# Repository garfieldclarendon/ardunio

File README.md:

# Layout Control System (LCS)

A project that uses ESP8266 WiFi modules that communicate with a Raspberry Pi server to control accessories on the Garfield-Clarendon Model Railroad Club.

### Prerequisites

The code running on the ESP8266 is developed using the Arduino IDE

The LCSServer application running on the Raspberry Pi makes use of the Qt framework.  The ESP8266 uses http calls to communicate with the LCSServer application  and UDP unicast messages to communicate with other ESP8266 controllers on the layout.  A separate RESTful API provides access to commands to activate routes, set turnouts and update data in the configuration database.

[Layout Control System Overview](https://github.com/garfieldclarendon/garfieldclarendon.github.io/blob/master/html/Documents/LCSOverview.pdf)

[Source Code Documentation](https://garfieldclarendon.github.io/html/index.html)

[API Documentation](https://garfieldclarendon.github.io/apidoc/index.html)

## Built With

* [Arduino](https://www.arduino.cc/en/Main/Software) - Arduino Tools
* [Qt](https://www.qt.io/) - Qt Framework
* [Eagle](https://www.autodesk.com/products/eagle/overview) - Eagle Printed Circuit Board (PCB) design software

## Contributing

Please read [CONTRIBUTING.md](https://gist.github.com/PurpleBooth/b24679402957c63ec426) for details on our code of conduct, and the process for submitting pull requests to us.

## Authors

* **John Reilly** - *Initial work*
* **Ryan Balla** - *Web Development*

## License

This project is licensed under the MIT License - see the [LICENSE](LICENSE) file for details

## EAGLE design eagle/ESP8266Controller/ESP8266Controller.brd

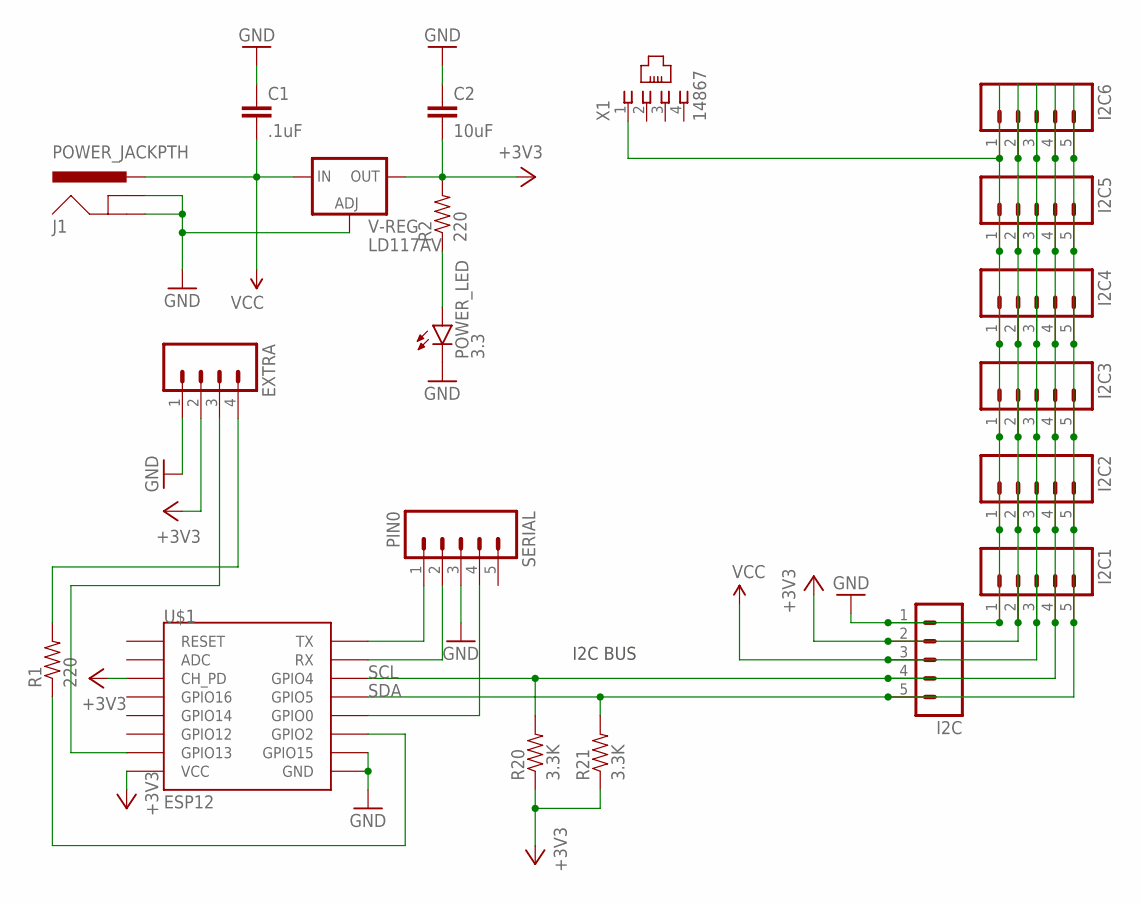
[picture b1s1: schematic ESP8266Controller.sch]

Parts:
C1: .1uF; CAP-PTH-SMALL
C2: 10uF; CAP-PTH-SMALL
EXTRA: M04; 04P
I2C, I2C1, I2C2, I2C3, I2C4, I2C5, I2C6: M05; 05P
J1: POWER_JACKPTH; POWER_JACK_PTH
POWER_LED: 3.3; LED5MM
R1, R2: 220; AXIAL-0.4
R20, R21: 3.3K; AXIAL-0.4
SERIAL: PIN0; 05P
U$1: ESP12
V-REG: LD117AV; TO220L1
X1: 14867

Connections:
+3V3: C2.2, EXTRA.2, I2C.2, I2C1.2, I2C2.2, I2C3.2, I2C4.2, I2C5.2, I2C6.2, R2.P$2 (2), R20.P$1 (1), R21.P$1 (1), U$1.CH_PD, U$1.VCC, V-REG.2 (OUT)
GND: C1.1, C2.1, EXTRA.1, I2C.1, I2C1.1, I2C2.1, I2C3.1, I2C4.1, I2C5.1, I2C6.1, J1.GND, J1.GNDBREAK, POWER_LED.K (C), SERIAL.3, U$1.GND, U$1.GPIO15, V-REG.1 (ADJ), X1.1
unnamed: EXTRA.4, R1.P$2 (2)
unnamed: R1.P$1 (1), U$1.GPIO2
unnamed: EXTRA.3, U$1.GPIO13
unnamed: SERIAL.1, U$1.TX
unnamed: POWER_LED.A, R2.P$1 (1)
unnamed: SERIAL.2, U$1.RX
unnamed: SERIAL.4, U$1.GPIO0
SCL: I2C.4, I2C1.4, I2C2.4, I2C3.4, I2C4.4, I2C5.4, I2C6.4, R20.P$2 (2), U$1.GPIO4
SDA: I2C.5, I2C1.5, I2C2.5, I2C3.5, I2C4.5, I2C5.5, I2C6.5, R21.P$2 (2), U$1.GPIO5
VCC: C1.2, I2C.3, I2C1.3, I2C2.3, I2C3.3, I2C4.3, I2C5.3, I2C6.3, J1.PWR, V-REG.3 (IN)

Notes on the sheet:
I2C BUS

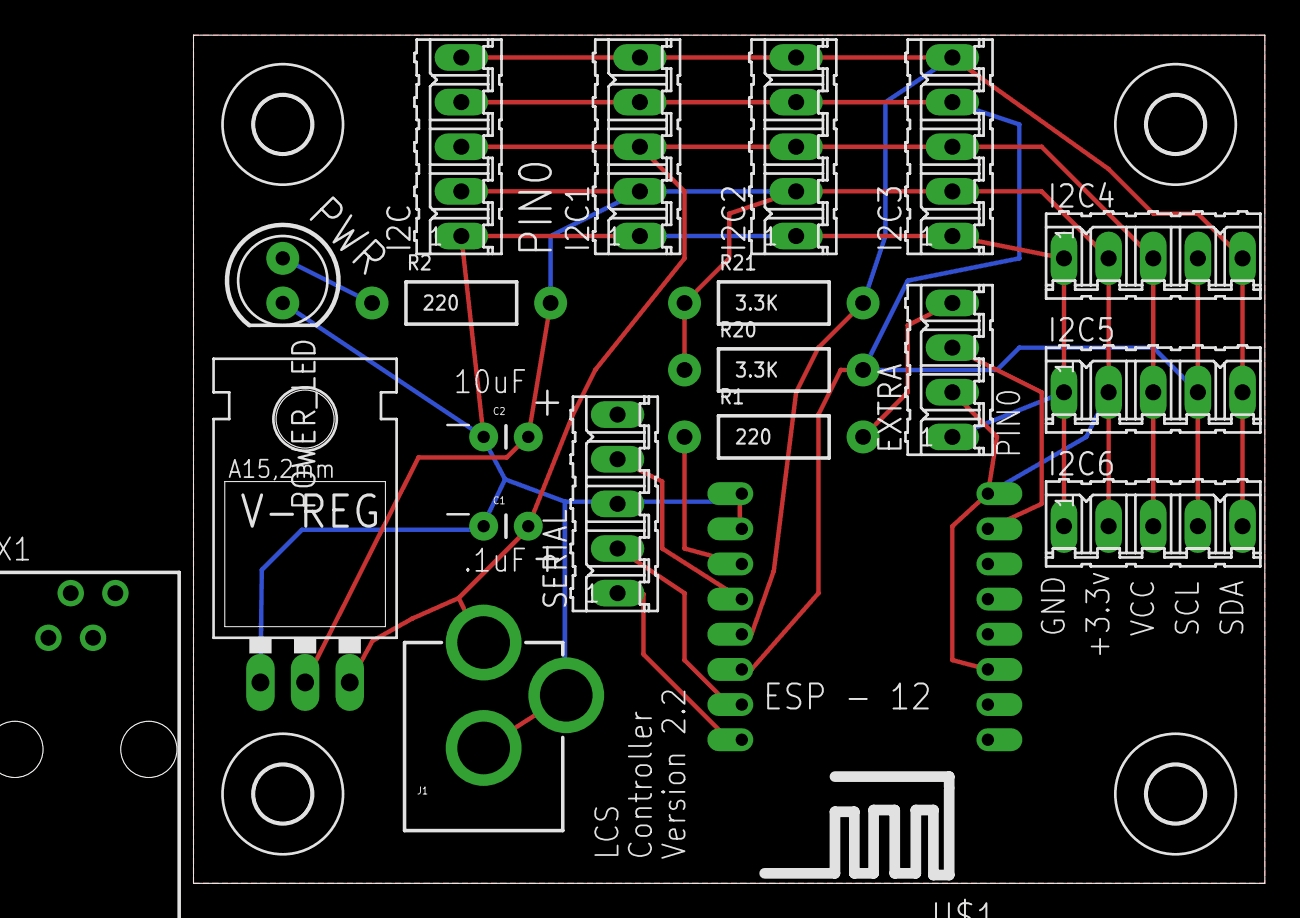
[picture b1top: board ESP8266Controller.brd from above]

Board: 2 copper layers, 61.0 x 48.3 mm, 24 parts (0 on the bottom side), 12 nets.

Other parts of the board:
U$2, U$3, U$4, U$5: 3,2

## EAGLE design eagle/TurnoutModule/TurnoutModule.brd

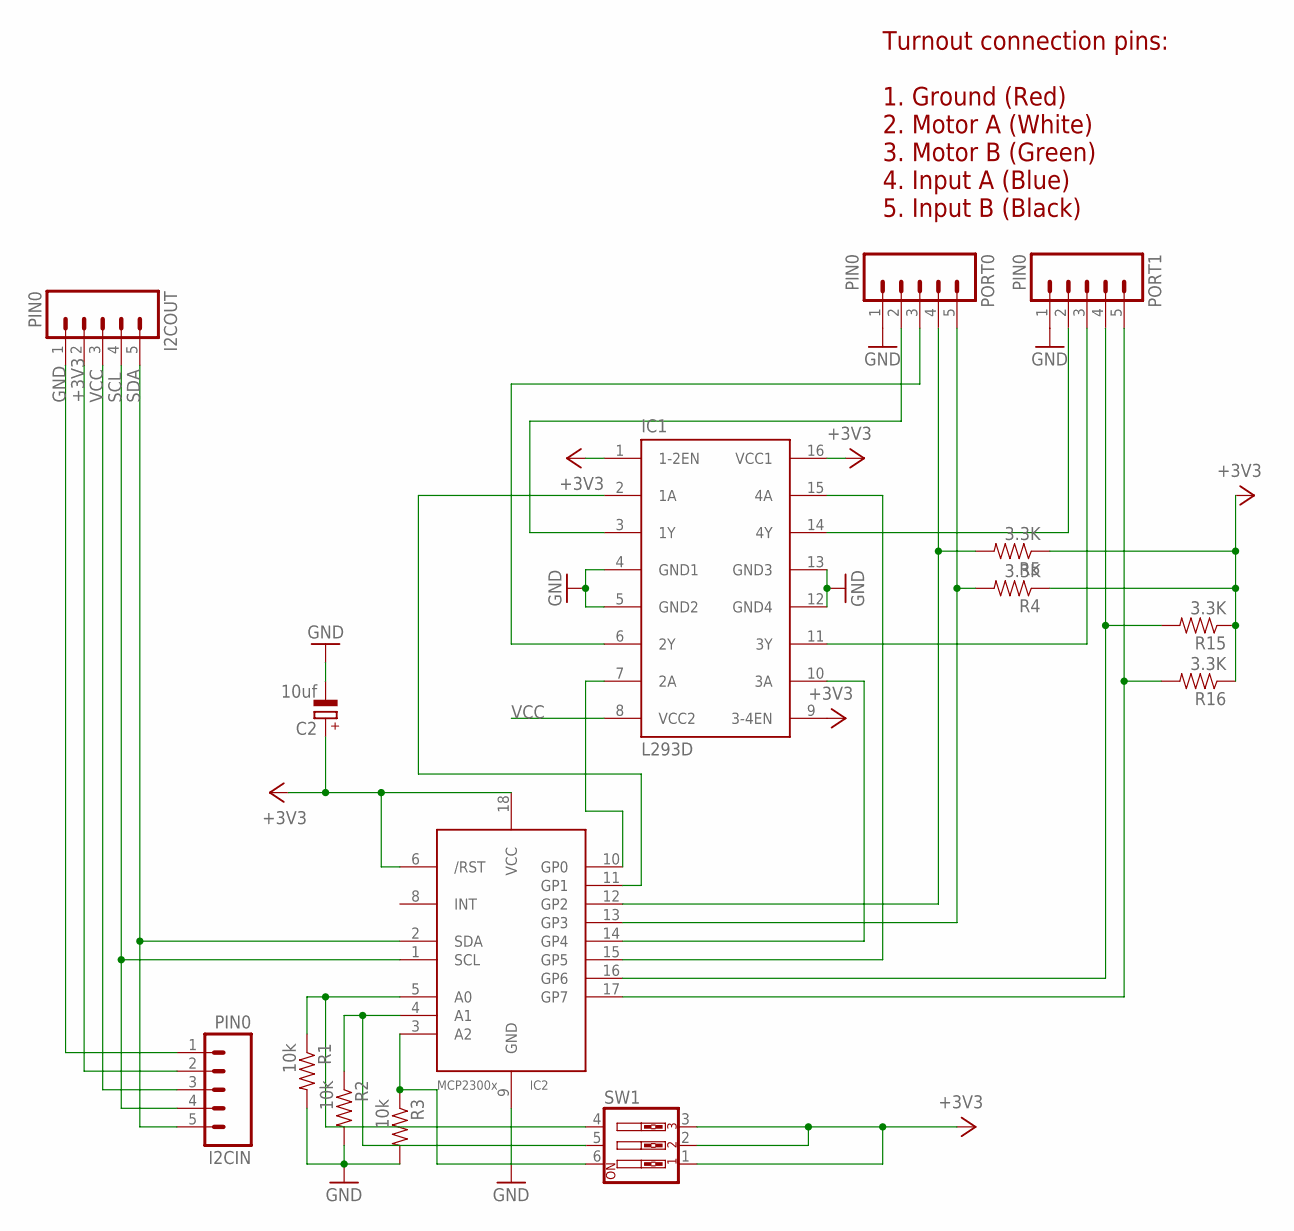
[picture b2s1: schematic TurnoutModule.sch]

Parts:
C2: 10uf; E2,5-6
I2CIN, I2COUT: PIN0; 05P
IC1: L293D; DIL16
IC2: MCP23008/P; DIL18
PORT0, PORT1: PIN0; 05P
R1, R2, R3: 10k; AXIAL-0.4
R4, R5, R15, R16: 3.3K; AXIAL-0.4
SW1: SW_DIP-3; EDG-03

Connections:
+3V3: C2.+, I2CIN.2, I2COUT.2, IC1.1 (1-2EN), IC1.9 (3-4EN), IC1.16 (VCC1), IC2.6 (/RST), IC2.18 (VCC), R4.P$1 (1), R5.P$1 (1), R15.P$1 (1), R16.P$1 (1), SW1.1, SW1.2, SW1.3
GND: C2.-, I2CIN.1, I2COUT.1, IC1.4 (GND1), IC1.5 (GND2), IC1.12 (GND4), IC1.13 (GND3), IC2.9 (GND), PORT0.1, PORT1.1, R1.P$2 (2), R2.P$2 (2), R3.P$2 (2)
unnamed: IC2.5 (A0), R1.P$1 (1), SW1.4
unnamed: IC2.17 (GP7), PORT1.5, R16.P$2 (2)
unnamed: IC1.3 (1Y), PORT0.2
unnamed: IC2.4 (A1), R2.P$1 (1), SW1.5
unnamed: IC2.16 (GP6), PORT1.4, R15.P$2 (2)
unnamed: IC1.6 (2Y), PORT0.3
unnamed: IC2.3 (A2), R3.P$1 (1), SW1.6
unnamed: IC1.7 (2A), IC2.10 (GP0)
unnamed: IC1.2 (1A), IC2.11 (GP1)
unnamed: IC1.14 (4Y), PORT1.2
unnamed: IC2.12 (GP2), PORT0.4, R5.P$2 (2)
unnamed: IC1.11 (3Y), PORT1.3
unnamed: IC1.10 (3A), IC2.14 (GP4)
unnamed: IC1.15 (4A), IC2.15 (GP5)
unnamed: IC2.13 (GP3), PORT0.5, R4.P$2 (2)
SCL: I2CIN.4, I2COUT.4, IC2.1 (SCL)
SDA: I2CIN.5, I2COUT.5, IC2.2 (SDA)
VCC: I2CIN.3, I2COUT.3, IC1.8 (VCC2)

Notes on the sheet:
Turnout connection pins: 1. Ground (Red) 2. Motor A (White) 3. Motor B (Green) 4. Input A (Blue) 5. Input B (Black)

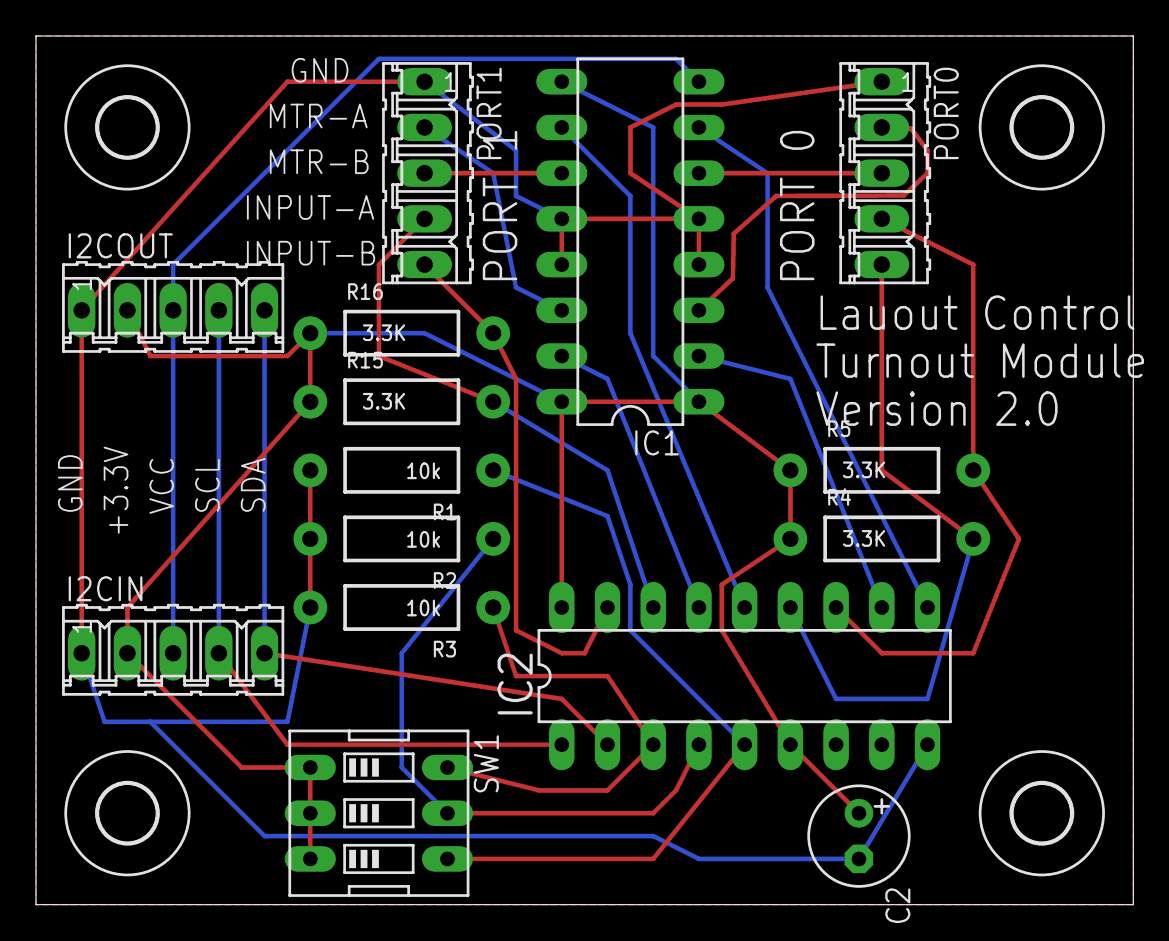
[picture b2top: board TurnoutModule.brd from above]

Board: 2 copper layers, 61.0 x 48.3 mm, 19 parts (0 on the bottom side), 20 nets.

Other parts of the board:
U$2, U$3, U$4, U$5: 3,2

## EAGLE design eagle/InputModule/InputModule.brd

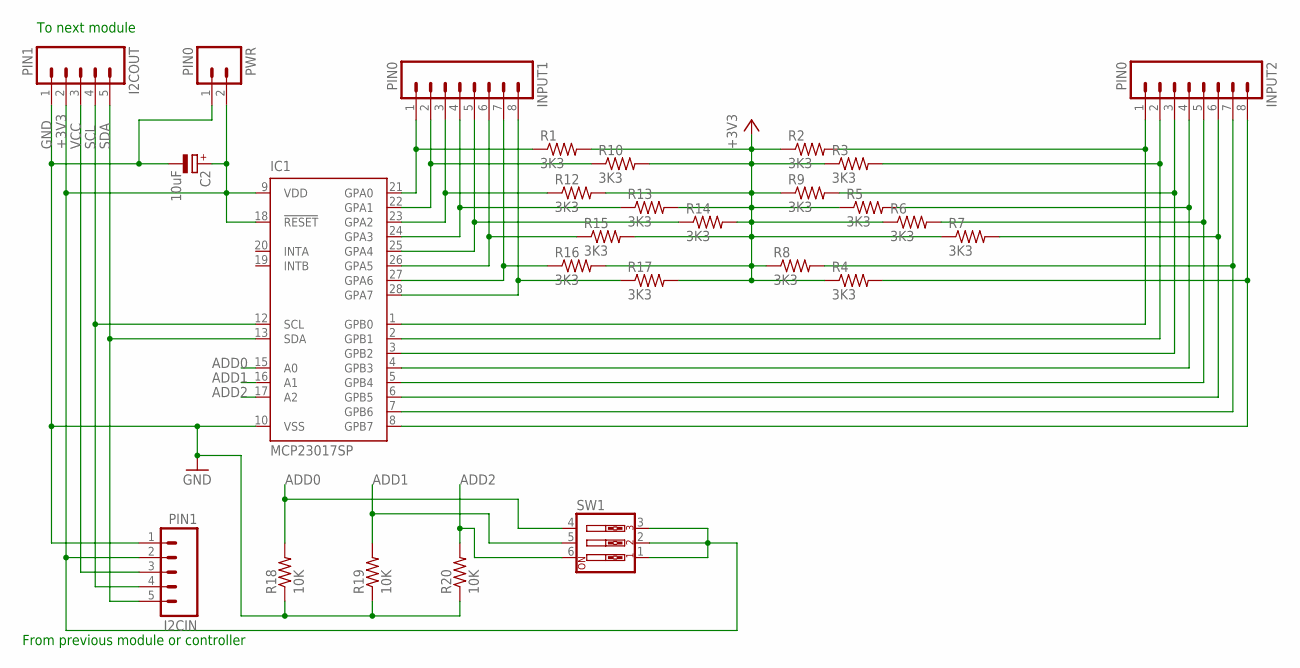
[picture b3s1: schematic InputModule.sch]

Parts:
C2: 10uF; E2,5-6
I2CIN, I2COUT: PIN1; 05P
IC1: MCP23017SP; DIL28-3
INPUT1, INPUT2: PIN0; 1X08_ROUND
PWR: PIN0; 02P
R1, R2, R3, R4, R5, R6, R7, R8, R9, R10, R12, R13, R14, R15, R16, R17: 3K3; AXIAL-0.4
R18, R19, R20: 10K; AXIAL-0.4
SW1: SW_DIP-3; EDG-03

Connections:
+3V3: C2.+, I2CIN.2, I2COUT.2, IC1.9 (VDD), IC1.18 (!RESET), PWR.2, R1.P$2 (2), R2.P$1 (1), R3.P$1 (1), R4.P$1 (1), R5.P$1 (1), R6.P$1 (1), R7.P$1 (1), R8.P$1 (1), R9.P$1 (1), R10.P$2 (2), R12.P$2 (2), R13.P$2 (2), R14.P$2 (2), R15.P$2 (2), R16.P$2 (2), R17.P$2 (2), SW1.1, SW1.2, SW1.3
ADD0: IC1.15 (A0), R18.P$2 (2), SW1.4
ADD1: IC1.16 (A1), R19.P$2 (2), SW1.5
ADD2: IC1.17 (A2), R20.P$2 (2), SW1.6
GND: C2.-, I2CIN.1, I2COUT.1, IC1.10 (VSS), PWR.1, R18.P$1 (1), R19.P$1 (1), R20.P$1 (1)
unnamed: IC1.1 (GPB0), INPUT2.1, R2.P$2 (2)
unnamed: IC1.2 (GPB1), INPUT2.2, R3.P$2 (2)
unnamed: IC1.3 (GPB2), INPUT2.3, R9.P$2 (2)
unnamed: IC1.4 (GPB3), INPUT2.4, R5.P$2 (2)
unnamed: IC1.5 (GPB4), INPUT2.5, R6.P$2 (2)
unnamed: IC1.6 (GPB5), INPUT2.6, R7.P$2 (2)
unnamed: IC1.7 (GPB6), INPUT2.7, R8.P$2 (2)
unnamed: IC1.8 (GPB7), INPUT2.8, R4.P$2 (2)
unnamed: IC1.21 (GPA0), INPUT1.1, R1.P$1 (1)
unnamed: IC1.22 (GPA1), INPUT1.2, R10.P$1 (1)
unnamed: IC1.23 (GPA2), INPUT1.3, R12.P$1 (1)
unnamed: IC1.24 (GPA3), INPUT1.4, R13.P$1 (1)
unnamed: IC1.25 (GPA4), INPUT1.5, R14.P$1 (1)
unnamed: IC1.26 (GPA5), INPUT1.6, R15.P$1 (1)
unnamed: IC1.27 (GPA6), INPUT1.7, R16.P$1 (1)
unnamed: IC1.28 (GPA7), INPUT1.8, R17.P$1 (1)
SCL: I2CIN.4, I2COUT.4, IC1.12 (SCL)
SDA: I2CIN.5, I2COUT.5, IC1.13 (SDA)
VCC: I2CIN.3, I2COUT.3

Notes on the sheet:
From previous module or controller
To next module

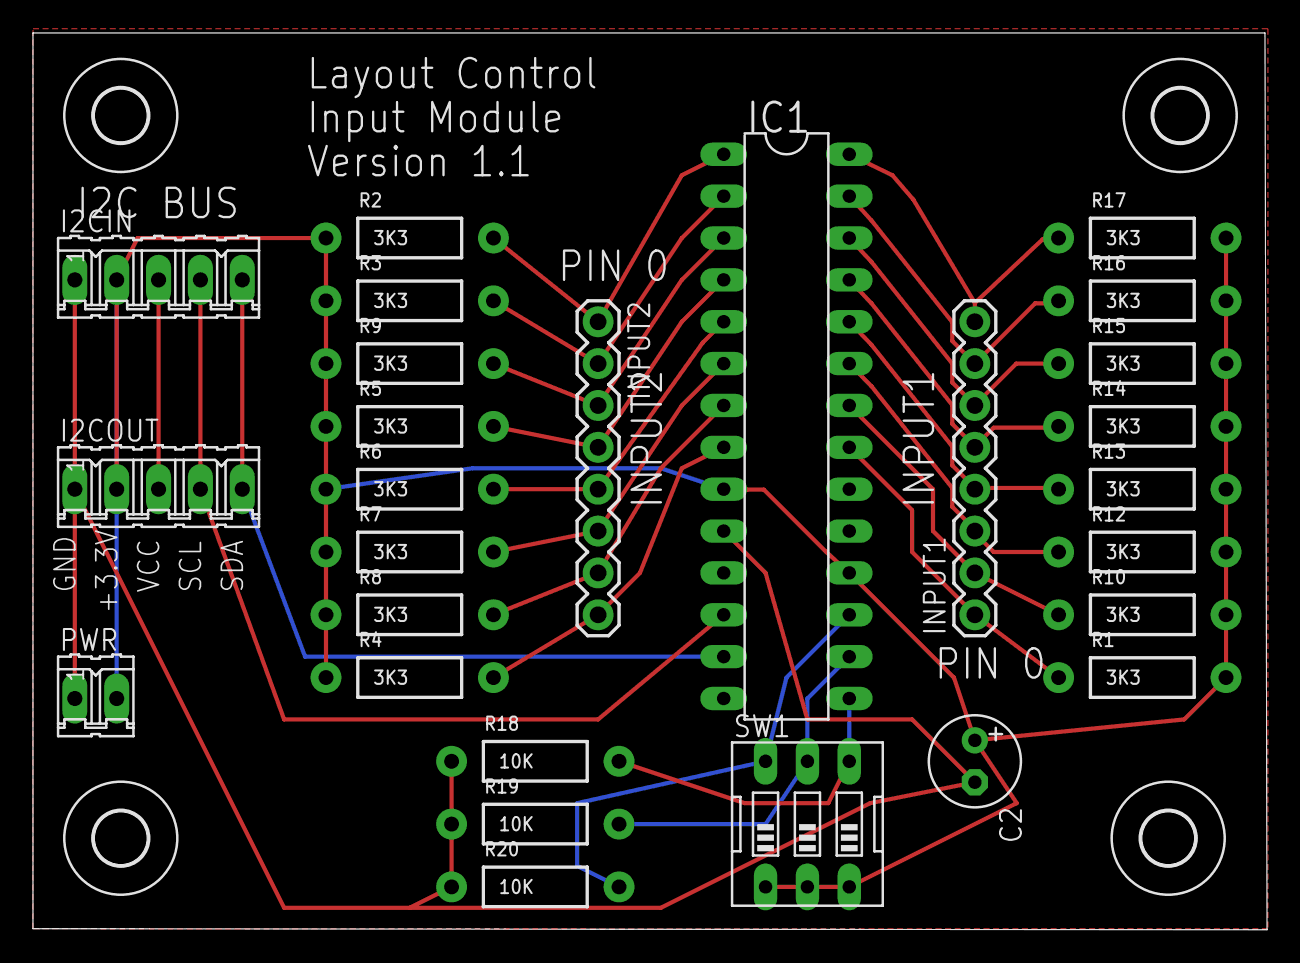
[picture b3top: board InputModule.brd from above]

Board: 2 copper layers, 74.9 x 54.4 mm, 31 parts (0 on the bottom side), 24 nets.

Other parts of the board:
U$1, U$2, U$3, U$4: 3,2

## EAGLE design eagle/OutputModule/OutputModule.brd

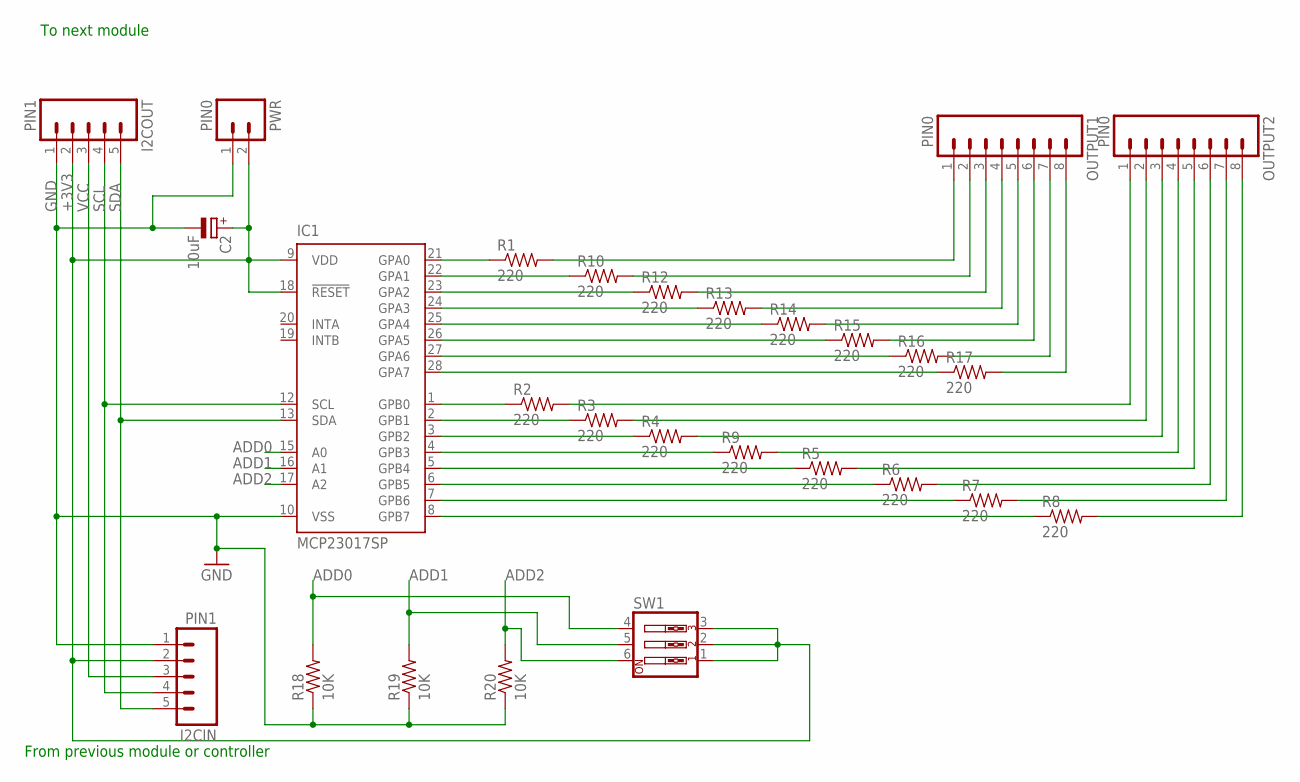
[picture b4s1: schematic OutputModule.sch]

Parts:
C2: 10uF; E2,5-6
I2CIN, I2COUT: PIN1; 05P
IC1: MCP23017SP; DIL28-3
OUTPUT1, OUTPUT2: PIN0; 1X08_ROUND
PWR: PIN0; 02P
R1, R2, R3, R4, R5, R6, R7, R8, R9, R10, R12, R13, R14, R15, R16, R17: 220; AXIAL-0.4
R18, R19, R20: 10K; AXIAL-0.4
SW1: SW_DIP-3; EDG-03

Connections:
+3V3: C2.+, I2CIN.2, I2COUT.2, IC1.9 (VDD), IC1.18 (!RESET), PWR.2, SW1.1, SW1.2, SW1.3
ADD0: IC1.15 (A0), R18.P$2 (2), SW1.4
ADD1: IC1.16 (A1), R19.P$2 (2), SW1.5
ADD2: IC1.17 (A2), R20.P$2 (2), SW1.6
GND: C2.-, I2CIN.1, I2COUT.1, IC1.10 (VSS), PWR.1, R18.P$1 (1), R19.P$1 (1), R20.P$1 (1)
unnamed: OUTPUT2.7, R7.P$2 (2)
unnamed: OUTPUT2.1, R2.P$2 (2)
unnamed: OUTPUT2.2, R3.P$2 (2)
unnamed: OUTPUT2.3, R4.P$2 (2)
unnamed: OUTPUT2.4, R9.P$2 (2)
unnamed: OUTPUT2.5, R5.P$2 (2)
unnamed: OUTPUT1.8, R17.P$2 (2)
unnamed: OUTPUT1.7, R16.P$2 (2)
unnamed: IC1.1 (GPB0), R2.P$1 (1)
unnamed: IC1.2 (GPB1), R3.P$1 (1)
unnamed: IC1.3 (GPB2), R4.P$1 (1)
unnamed: IC1.5 (GPB4), R5.P$1 (1)
unnamed: IC1.6 (GPB5), R6.P$1 (1)
unnamed: IC1.7 (GPB6), R7.P$1 (1)
unnamed: IC1.8 (GPB7), R8.P$1 (1)
unnamed: OUTPUT2.6, R6.P$2 (2)
unnamed: IC1.4 (GPB3), R9.P$1 (1)
unnamed: OUTPUT2.8, R8.P$2 (2)
unnamed: IC1.21 (GPA0), R1.P$1 (1)
unnamed: IC1.22 (GPA1), R10.P$1 (1)
unnamed: IC1.23 (GPA2), R12.P$1 (1)
unnamed: IC1.24 (GPA3), R13.P$1 (1)
unnamed: IC1.25 (GPA4), R14.P$1 (1)
unnamed: IC1.26 (GPA5), R15.P$1 (1)
unnamed: IC1.27 (GPA6), R16.P$1 (1)
unnamed: IC1.28 (GPA7), R17.P$1 (1)
unnamed: OUTPUT1.6, R15.P$2 (2)
unnamed: OUTPUT1.5, R14.P$2 (2)
unnamed: OUTPUT1.4, R13.P$2 (2)
unnamed: OUTPUT1.3, R12.P$2 (2)
unnamed: OUTPUT1.2, R10.P$2 (2)
unnamed: OUTPUT1.1, R1.P$2 (2)
SCL: I2CIN.4, I2COUT.4, IC1.12 (SCL)
SDA: I2CIN.5, I2COUT.5, IC1.13 (SDA)
VCC: I2CIN.3, I2COUT.3

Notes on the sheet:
From previous module or controller
To next module

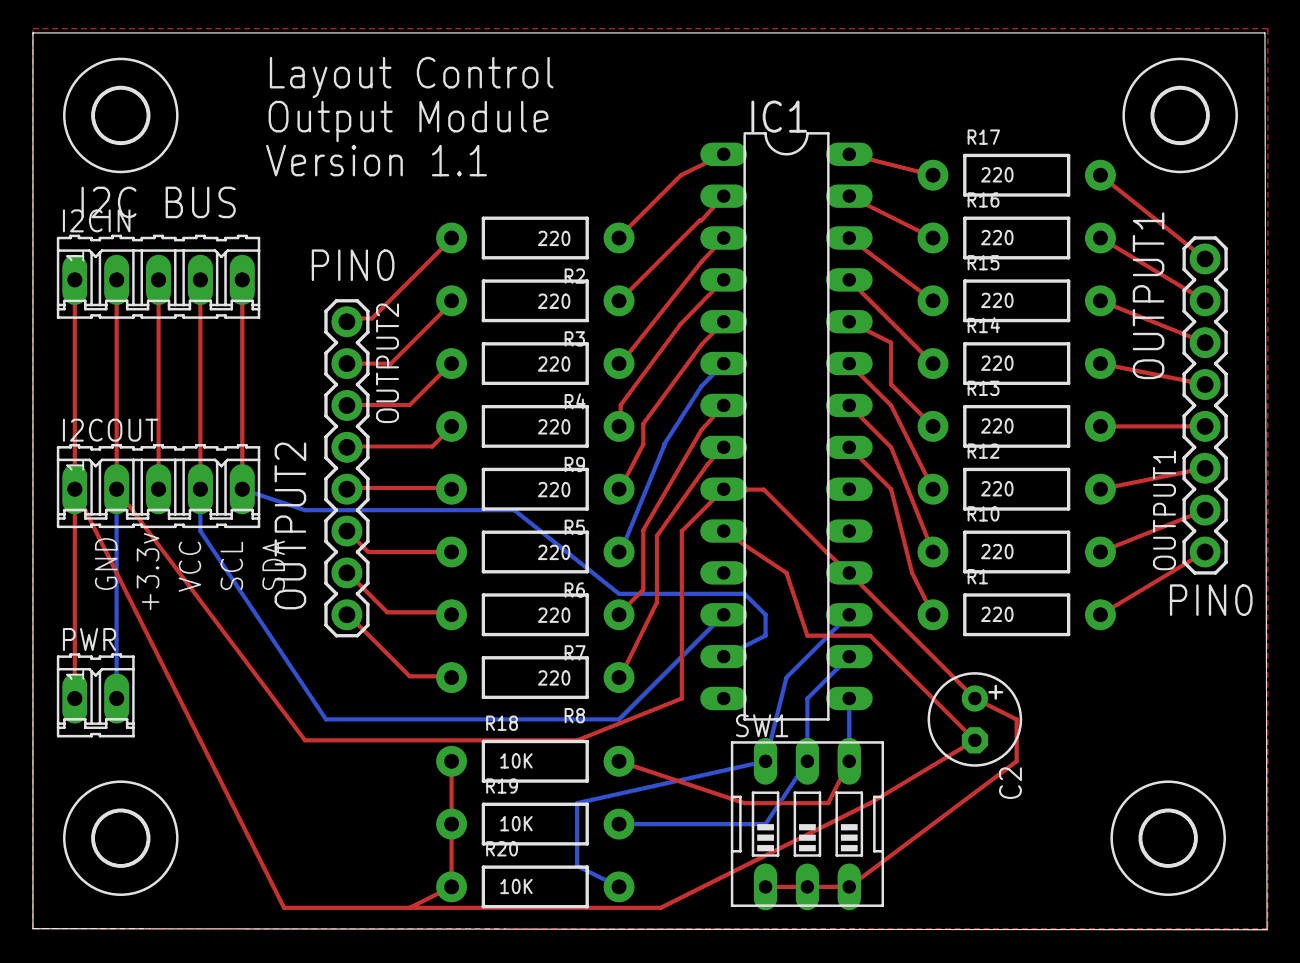
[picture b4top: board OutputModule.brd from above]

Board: 2 copper layers, 74.9 x 54.4 mm, 31 parts (0 on the bottom side), 40 nets.

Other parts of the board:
U$1, U$2, U$3, U$4: 3,2

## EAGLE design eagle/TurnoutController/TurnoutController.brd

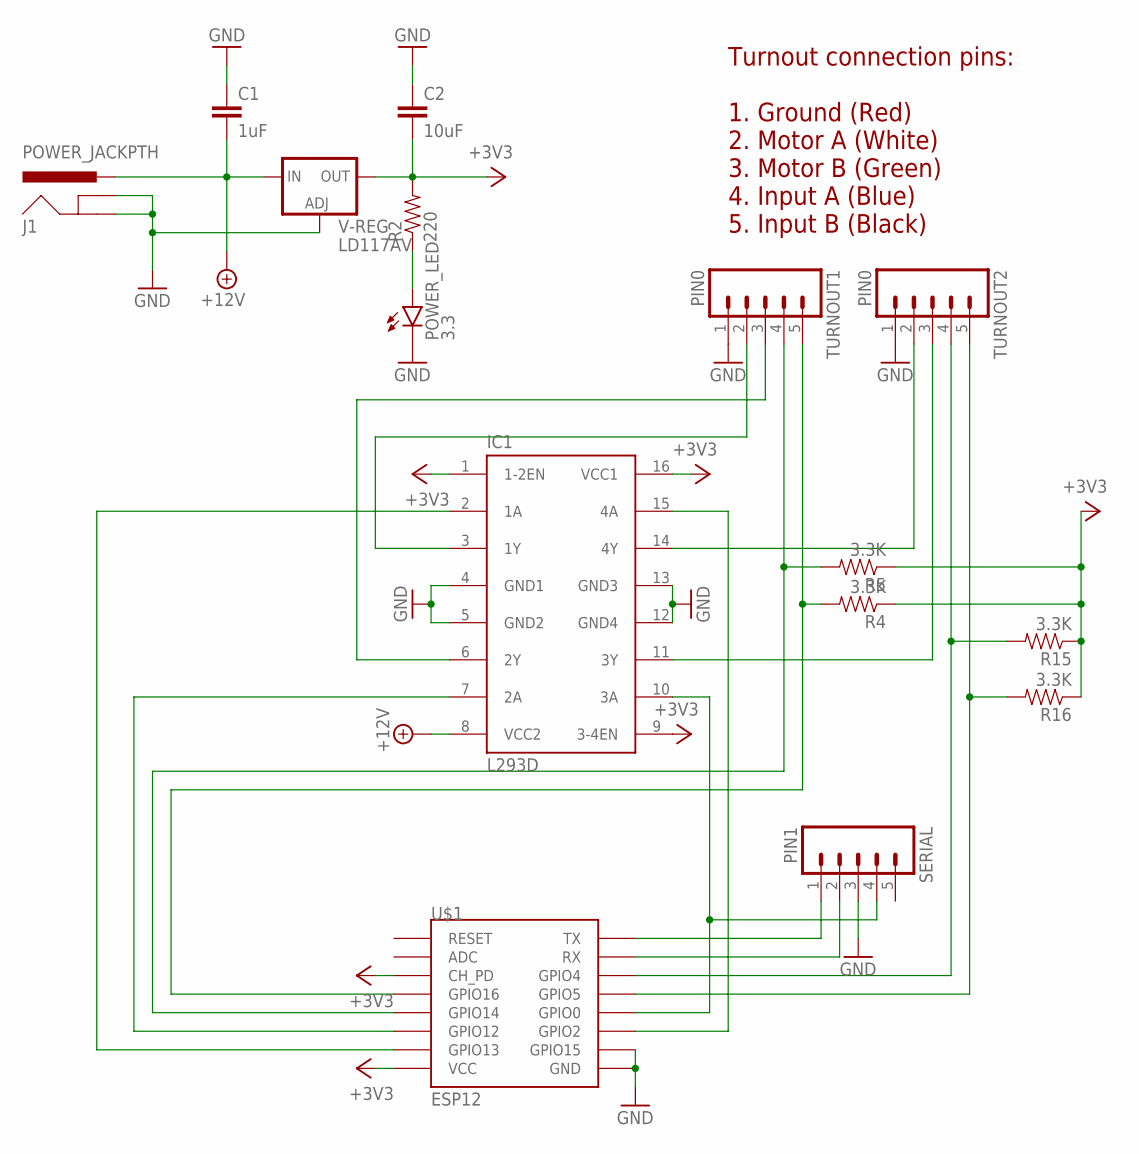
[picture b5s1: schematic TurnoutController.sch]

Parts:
C1: 1uF; CAP-PTH-SMALL
C2: 10uF; CAP-PTH-SMALL
IC1: L293D; DIL16
J1: POWER_JACKPTH; POWER_JACK_PTH
POWER_LED: 3.3; LED5MM
R2: 220; AXIAL-0.4
R4, R5, R15, R16: 3.3K; AXIAL-0.4
SERIAL: PIN1; 05P
TURNOUT1, TURNOUT2: PIN0; 05P
U$1: ESP12
V-REG: LD117AV; TO220L1

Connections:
+3V3: C2.2, IC1.1 (1-2EN), IC1.9 (3-4EN), IC1.16 (VCC1), R2.P$2 (2), R4.P$1 (1), R5.P$1 (1), R15.P$1 (1), R16.P$1 (1), U$1.CH_PD, U$1.VCC, V-REG.2 (OUT)
+12V: C1.2, IC1.8 (VCC2), J1.PWR, V-REG.3 (IN)
GND: C1.1, C2.1, IC1.4 (GND1), IC1.5 (GND2), IC1.12 (GND4), IC1.13 (GND3), J1.GND, J1.GNDBREAK, POWER_LED.K (C), SERIAL.3, TURNOUT1.1, TURNOUT2.1, U$1.GND, U$1.GPIO15, V-REG.1 (ADJ)
unnamed: R16.P$2 (2), TURNOUT2.5, U$1.GPIO5
unnamed: IC1.3 (1Y), TURNOUT1.2
unnamed: SERIAL.1, U$1.TX
unnamed: R15.P$2 (2), TURNOUT2.4, U$1.GPIO4
unnamed: IC1.6 (2Y), TURNOUT1.3
unnamed: POWER_LED.A, R2.P$1 (1)
unnamed: IC1.7 (2A), U$1.GPIO12
unnamed: IC1.2 (1A), U$1.GPIO13
unnamed: IC1.14 (4Y), TURNOUT2.2
unnamed: SERIAL.2, U$1.RX
unnamed: R5.P$2 (2), TURNOUT1.4, U$1.GPIO14
unnamed: IC1.11 (3Y), TURNOUT2.3
unnamed: IC1.10 (3A), SERIAL.4, U$1.GPIO0
unnamed: IC1.15 (4A), U$1.GPIO2
unnamed: R4.P$2 (2), TURNOUT1.5, U$1.GPIO16

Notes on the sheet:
Turnout connection pins: 1. Ground (Red) 2. Motor A (White) 3. Motor B (Green) 4. Input A (Blue) 5. Input B (Black)

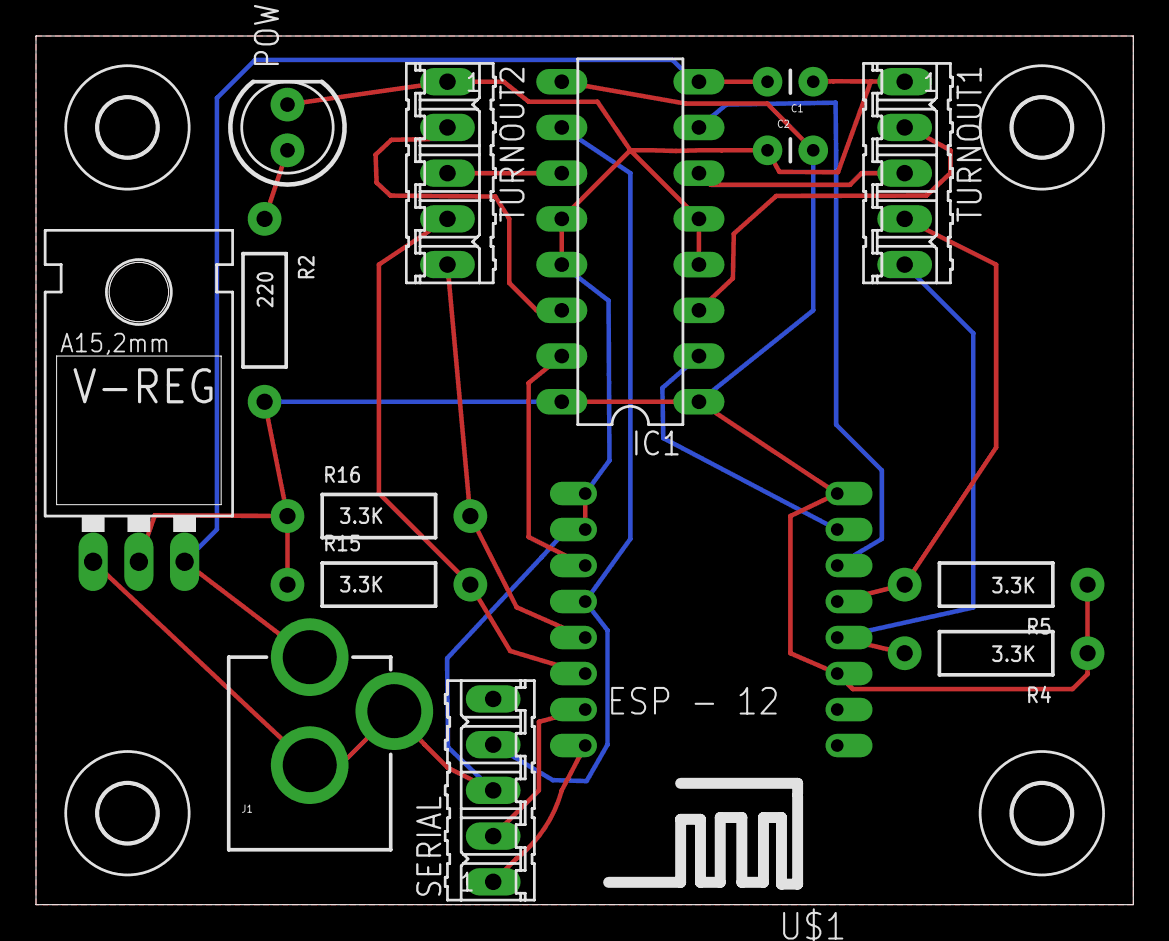
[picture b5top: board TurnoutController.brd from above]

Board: 2 copper layers, 61.0 x 48.3 mm, 19 parts (0 on the bottom side), 18 nets.

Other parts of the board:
U$2, U$3, U$4, U$5: 3,2

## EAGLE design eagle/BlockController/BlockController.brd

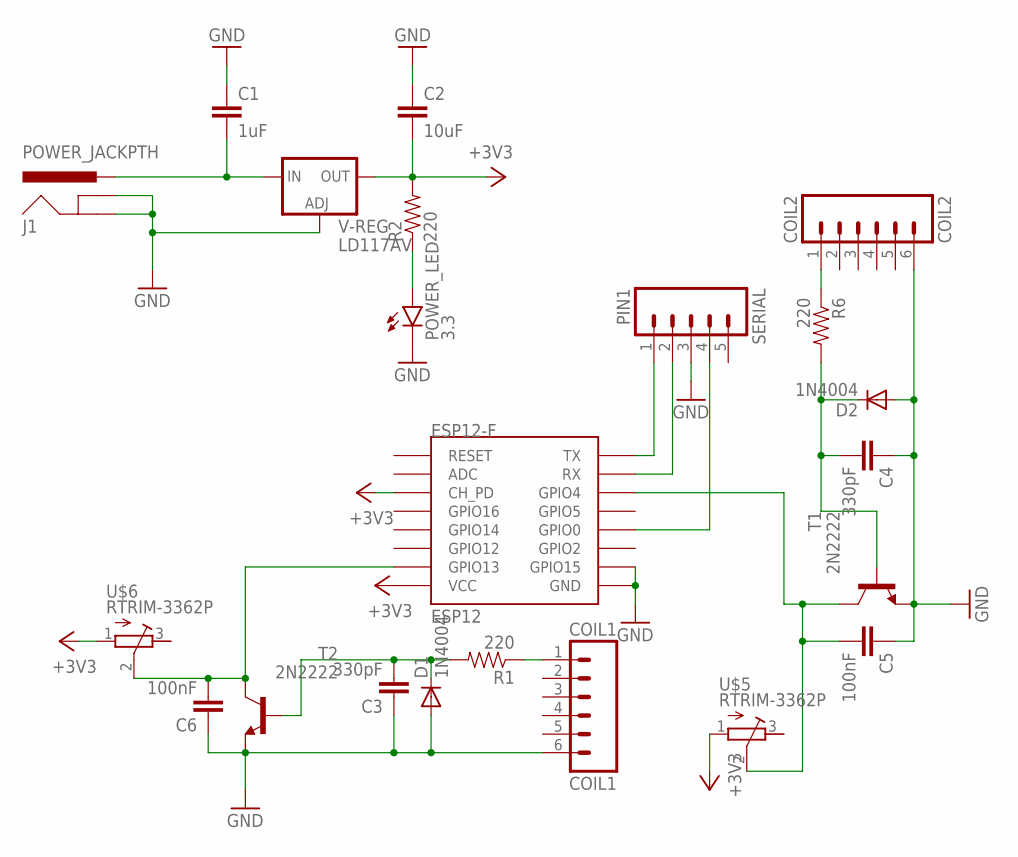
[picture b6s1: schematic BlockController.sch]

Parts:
C1: 1uF; CAP-PTH-SMALL
C2: 10uF; CAP-PTH-SMALL
C3, C4: 330pF; CAP-PTH-SMALL
C5, C6: 100nF; CAP-PTH-SMALL
COIL1: COIL1; 06P
COIL2: COIL2; 06P
D1, D2: 1N4004; DO41-10
ESP12-F: ESP12
J1: POWER_JACKPTH; POWER_JACK_PTH
POWER_LED: 3.3; LED5MM
R1, R2, R6: 220; AXIAL-0.4
SERIAL: PIN1; 05P
T1, T2: 2N2222; TO18
U$5, U$6: RTRIM-3362P; RTRIM3362P
V-REG: LD117AV; TO220L1

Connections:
+3V3: C2.2, ESP12-F.CH_PD, ESP12-F.VCC, R2.P$2 (2), U$5.1, U$6.1, V-REG.2 (OUT)
GND: C1.1, C2.1, C3.1, C4.1, C5.1, C6.1, COIL1.6, COIL2.6, D1.A, D2.A, ESP12-F.GND, ESP12-F.GPIO15, J1.GND, J1.GNDBREAK, POWER_LED.K (C), SERIAL.3, T1.1 (E), T2.1 (E), V-REG.1 (ADJ)
unnamed: COIL1.1, R1.P$1 (1)
unnamed: C3.2, D1.C, R1.P$2 (2), T2.2 (B)
unnamed: C4.2, D2.C, R6.P$2 (2), T1.2 (B)
unnamed: COIL2.1, R6.P$1 (1)
unnamed: C5.2, ESP12-F.GPIO4, T1.3 (C), U$5.2
unnamed: POWER_LED.A, R2.P$1 (1)
unnamed: ESP12-F.TX, SERIAL.1
unnamed: ESP12-F.RX, SERIAL.2
unnamed: ESP12-F.GPIO0, SERIAL.4
unnamed: C1.2, J1.PWR, V-REG.3 (IN)
unnamed: C6.2, ESP12-F.GPIO13, T2.3 (C), U$6.2

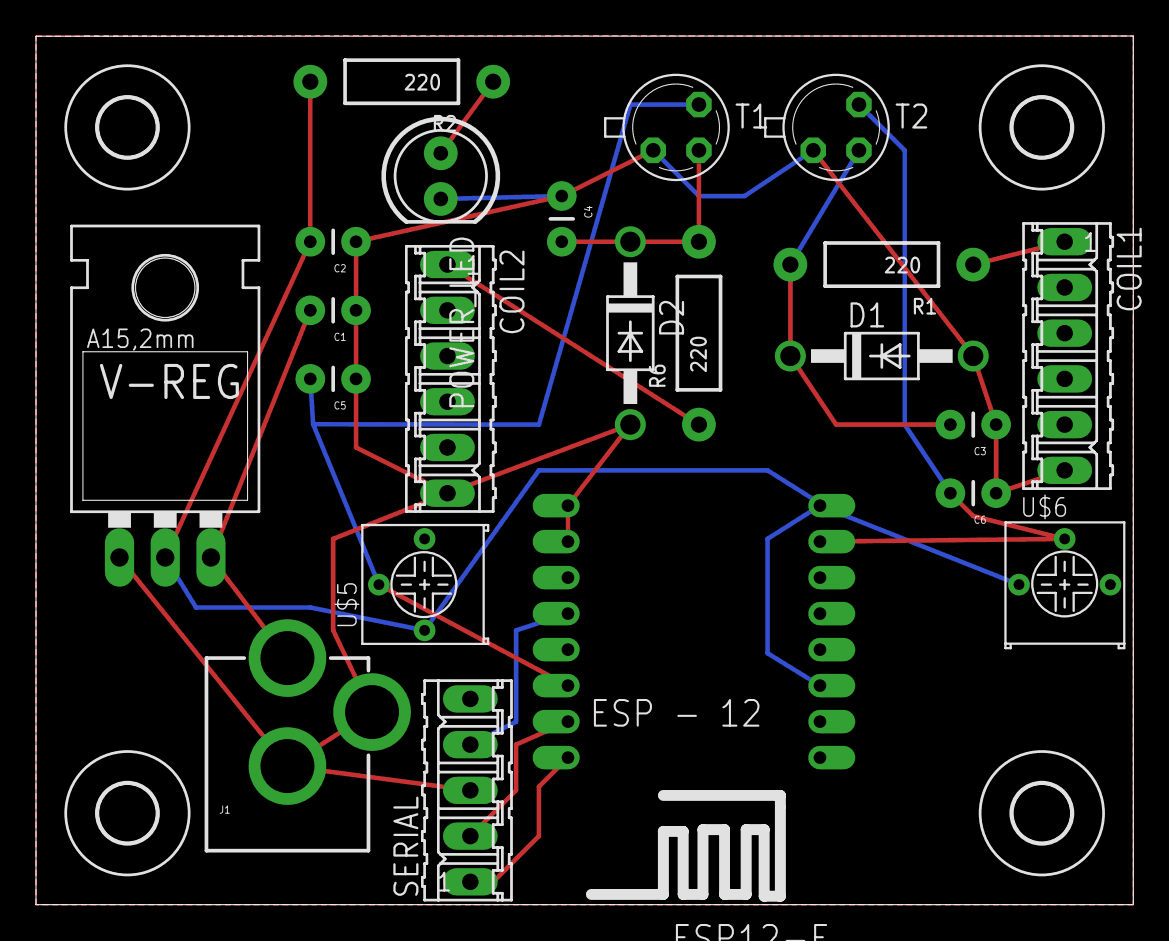
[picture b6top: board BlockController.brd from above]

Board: 2 copper layers, 61.0 x 48.3 mm, 26 parts (0 on the bottom side), 13 nets.

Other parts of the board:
U$1, U$2, U$3, U$4: 3,2

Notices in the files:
parts and their libraries:
SparkFun-Capacitors: Licensing: Creative Commons ShareAlike 4.0 International - https://creativecommons.org/licenses/by-sa/4.0
